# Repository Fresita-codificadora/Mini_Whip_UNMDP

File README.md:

# Mini_Whip_UNMDP
Repositorio para dejar los archivos pertinentes a un desarrollo de una antena Mini Whip basada en el diseño "pa0rdt-Mini-Whip"

## Amplificador_MiniWhip_original_j310

Esta carpeta contiene archivos de simulación sobre el diseño original "pa0rdt-Mini-Whip" donde se evaluó comportamiento, ancho de banda, ganancia, resistencia de entrada y puntos de polarización. 

## Amplificador_MiniWhip_segunda y tercera opcion

Esta carpeta Esta carpeta contiene archivos de simulación sobre modificaciones en el diseño original "pa0rdt-Mini-Whip" donde se evaluó comportamiento, ancho de banda, ganancia, resistencia de entrada y puntos de polarización para otros componentes ya que en Argentina se dificulta conseguir los componentes originales

## Gerber_Antenna Mini-Whip PCB (TH)_Main module_2020-09-29_11-44-25

Esta carpeta contiene esquematicos y un proyecto de "EasyEDA" para la contrucción de la antena Mini Whip original de autoria IgrikXD en su repositorio de Github 
https://github.com/IgrikXD/Easy-SDR

!!!!!!!!!!NO ES DE MI AUTORIA¡¡¡¡¡¡¡¡¡¡

## MiniWhip_con_2N7000

Esta carpeta contiene archivos de simulación del amplificador utilizando transistores comunes como el 2N7000 y el 2N2222 donde se evaluó viabilidad, comportamiento, ancho de banda, ganancia, resistencia de entrada y puntos de polarización. Ya que en Argentina se dificulta conseguir los componentes originales

Este diseño nace del archivo "Inspiracion 2N7000.pdf" donde se muestra un circuito con el 2N7000.

## miniwhip_kicad

Esta carpeta contiene un proyecto de kicad con el diseño original de "pa0rdt-Mini-Whip", de mi autoria, basado en los esquematicos de IgrikXD y consideraciones personales junto con los ingenieros de la UNMDP.

              #Power_1 es la fuente para la antena activa que utiliza un diodo
              
              #Power_2 es la fuente para la antena activa que utiliza un transformador
              
## PDFs

Los pdf en esta carpeta fueron utilizados como material de investigación e inspiración.

# LINKS DE INTERÉS

## proyecto original

https://github.com/IgrikXD/Easy-SDR/tree/master/Antenna%20Mini-Whip

https://oshwlab.com/IgrikXD/Antenna_Mini_Whip_SMD-74e9e6740b814f6c901a811855125754

## Tierra en las miniwhips

http://pa3fwm.nl/technotes/tn09d.html

## video muy interesante sobre el desarrollo y construcción de una miniwhip

https://www.youtube.com/watch?v=uFUlopjSGo4

## Funcionamiento de la miniwhip especificamente de la pa0rdt

http://www.pa3fwm.nl/technotes/tn07.html

http://dl1dbc.net/SAQ/miniwhip.html

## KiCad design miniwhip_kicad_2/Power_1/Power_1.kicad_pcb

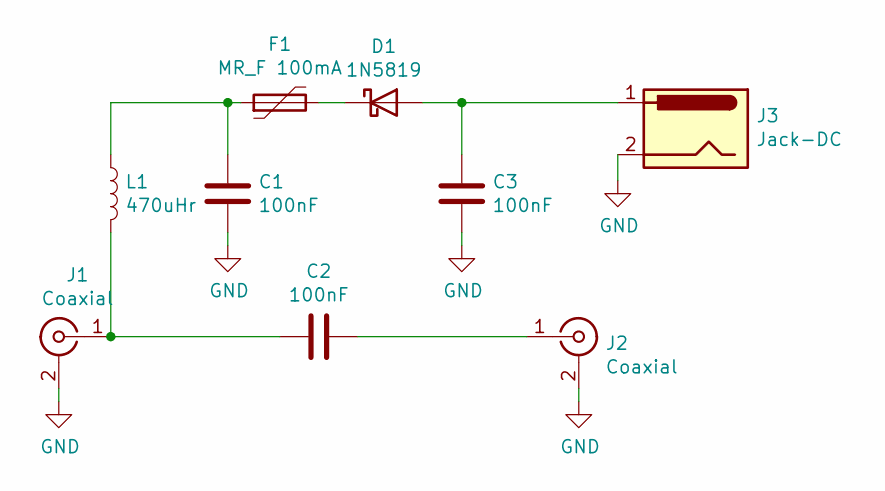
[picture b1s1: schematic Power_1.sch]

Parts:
C1, C2, C3: 100nF; C_Disc_D6.0mm_W2.5mm_P5.00mm
D1: 1N5819; D_DO-41_SOD81_P10.16mm_Horizontal
F1: MR_F 100mA; Fuse_BelFuse_0ZRE0016FF_L9.9mm_W3.8mm
J1, J2: Coaxial; BNC_Amphenol_031-6575_Horizontal
J3: Jack-DC; BarrelJack_Horizontal
L1: 470uHr; L_Axial_L6.6mm_D2.7mm_P10.16mm_Horizontal_Vishay_IM-2

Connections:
GND: C1.2, C3.2, J1.2 (Ext), J1.3, J1.4, J2.2 (Ext), J2.3, J2.4, J3.2, J3.3
unnamed: C1.1, F1.1, L1.1
unnamed: C2.1, J1.1 (In), L1.2
unnamed: C2.2, J2.1 (In)
unnamed: C3.1, D1.2 (A), J3.1
unnamed: D1.1 (K), F1.2

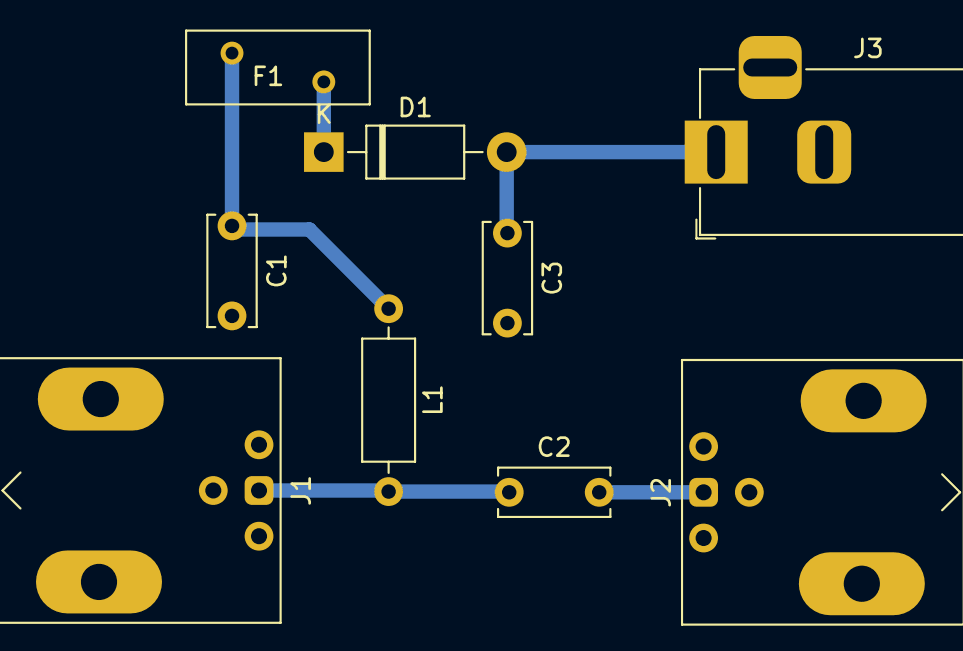
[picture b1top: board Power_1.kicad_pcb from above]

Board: 2 copper layers, 9 parts (0 on the bottom side), 6 nets.

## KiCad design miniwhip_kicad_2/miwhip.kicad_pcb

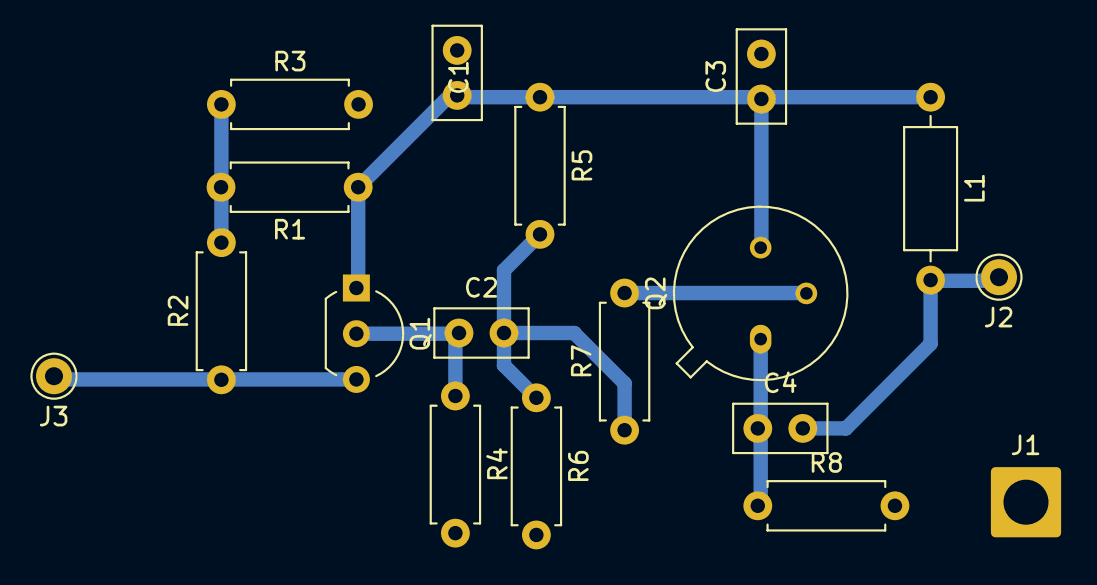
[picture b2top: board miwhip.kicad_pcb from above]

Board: 2 copper layers, 18 parts (0 on the bottom side), 9 nets.

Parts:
C1, C2, C3, C4: 100nF; C_Disc_D5.0mm_W2.5mm_P2.50mm
J1: PORT; SolderWire-2sqmm_1x01_D2mm_OD3.9mm
J2, J3: Coaxial; Pin_D1.0mm_L10.0mm
L1: 470uHr; L_Axial_L6.6mm_D2.7mm_P10.16mm_Horizontal_Vishay_IM-2
Q1: J310; TO-92L_Inline_Wide
Q2: 2N5109; TO-39-3
R1, R2, R3: 1M; R_Axial_DIN0207_L6.3mm_D2.5mm_P7.62mm_Horizontal
R4: 680R; R_Axial_DIN0207_L6.3mm_D2.5mm_P7.62mm_Horizontal
R5: 2k2; R_Axial_DIN0207_L6.3mm_D2.5mm_P7.62mm_Horizontal
R6: 10k; R_Axial_DIN0207_L6.3mm_D2.5mm_P7.62mm_Horizontal
R7: 47R; R_Axial_DIN0207_L6.3mm_D2.5mm_P7.62mm_Horizontal
R8: 220R; R_Axial_DIN0207_L6.3mm_D2.5mm_P7.62mm_Horizontal

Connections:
Antenna: J3.1 (In), Q1.3 (G), R2.1
Earth: C1.2, C3.2, J1.1, R3.2, R4.2, R6.2, R8.2
unnamed: C2.2, R5.2, R6.1, R7.1
unnamed: C4.2, J2.1 (In), L1.2
unnamed: C1.1, C3.1, L1.1, Q1.1 (D), Q2.3 (C), R1.1, R5.1
unnamed: C2.1, Q1.2 (S), R4.1
unnamed: Q2.2 (B), R7.2
unnamed: C4.1, Q2.1 (E), R8.1
unnamed: R1.2, R2.2, R3.1

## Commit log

2023-09-07 README.md
2023-09-09 Rename Gerber_BoardOutline.GKO to Gerber_BoardOutline.GKO
2024-04-28 cambios en los modelos de simulacion
